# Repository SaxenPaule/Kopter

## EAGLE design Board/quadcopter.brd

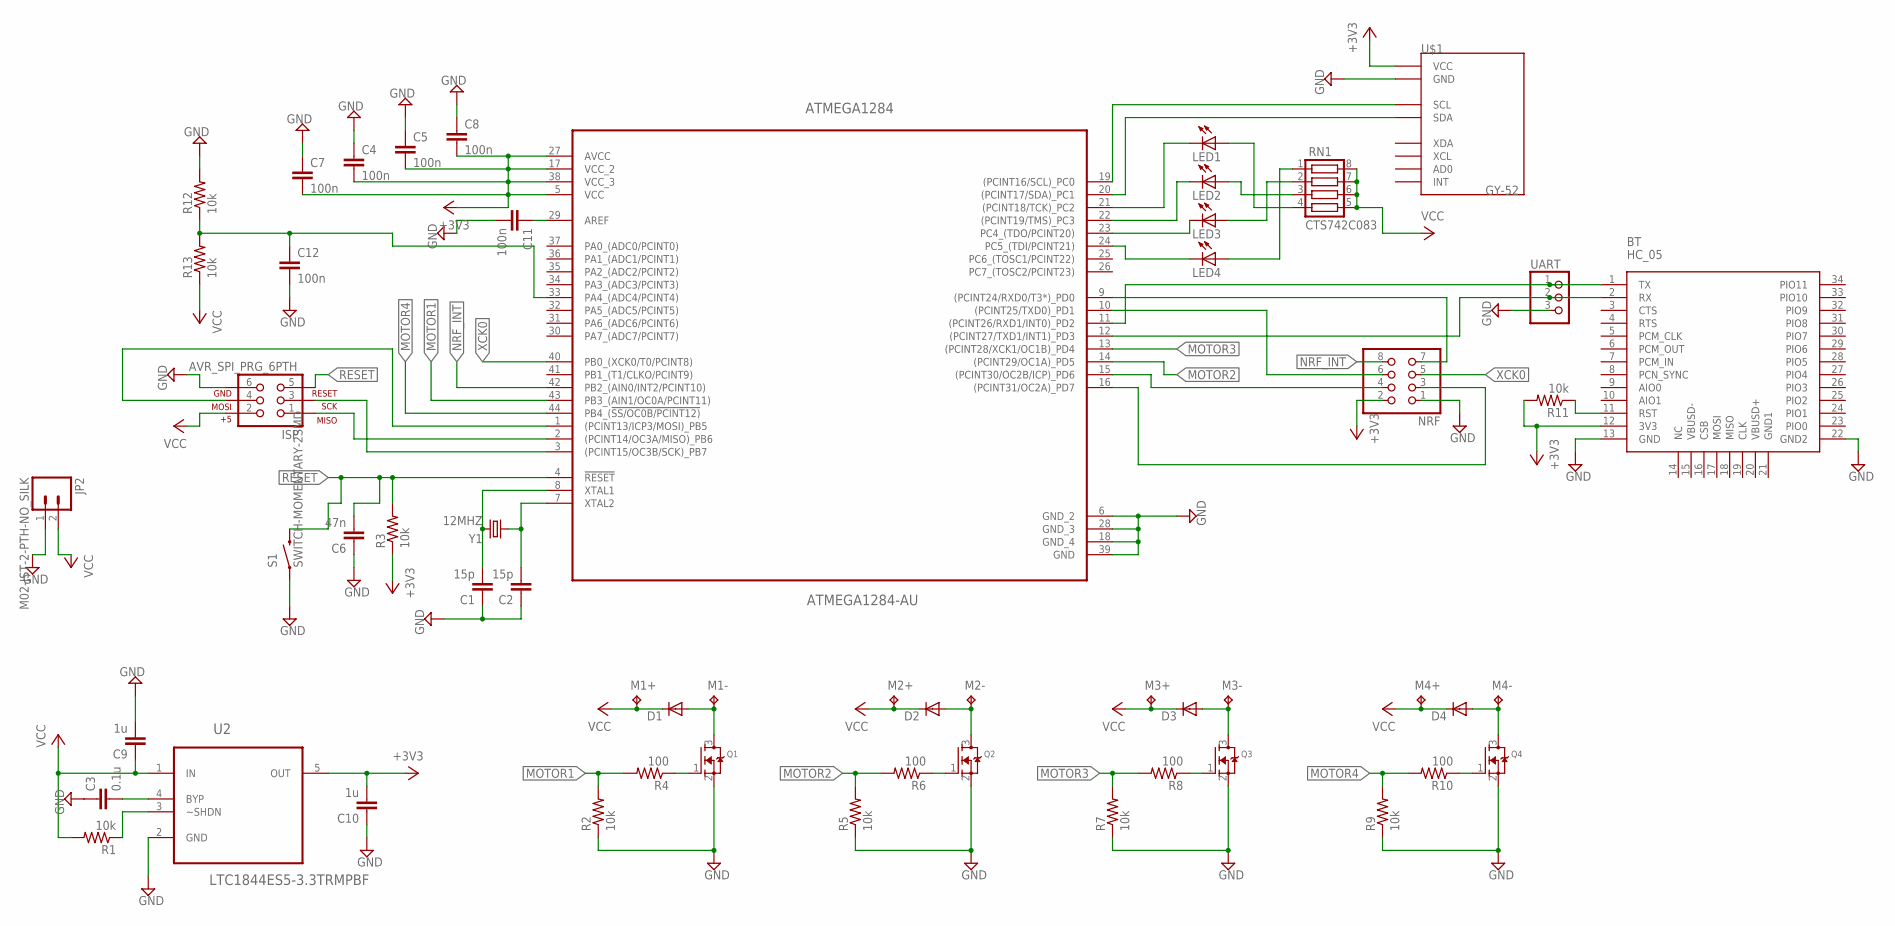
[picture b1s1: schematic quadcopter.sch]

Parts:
ATMEGA1284: ATMEGA1284-AU; QFP80P1200X1200X120-44N
BT: HC_05; BLUETOOTH_SMD
C1, C2: 15p; 0603-CAP
C3: 0.1u; 0603-CAP
C4, C5, C7, C8, C11, C12: 100n; 0603-CAP
C6: 47n; 0603-CAP
C9, C10: 1u; 0603-CAP
D1, D2, D3, D4: DIODE-SMB; SMB
ISP: AVR_SPI_PRG_6PTH; 2X3
JP2: M02-JST-2-PTH-NO_SILK; JST-2-PTH-NS
LED1, LED2, LED3, LED4: LEDCHIP-LED0805; CHIP-LED0805
M1+, M1-, M2+, M2-, M3+, M3-, M4+, M4-: TPTP20SQ; TP20SQ
NRF: PINHD-2X4; 2X04
Q1, Q2, Q3, Q4: MOSFET-NREFLOW; SOT23
R1, R2, R3, R5, R7, R9, R11, R12, R13: 10k; 0603-RES
R4, R6, R8, R10: 100; 0603-RES
RN1: CTS742C083
S1: SWITCH-MOMENTARY-2SMD; TACTILE_SWITCH_SMD
U2: LTC1844ES5-3.3TRMPBF; SOT95P280X100-5N
U$1: GY-52; PDIP-8
UART: PINHD-1X3; 1X03
Y1: 12MHZ; TXC-SMD-CRYSTAL

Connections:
+3V3: ATMEGA1284.5 (VCC), ATMEGA1284.17 (VCC_2), ATMEGA1284.27 (AVCC), ATMEGA1284.38 (VCC_3), BT.12 (3V3), C4.2, C5.2, C7.2, C8.2, C10.2, NRF.2, R3.1, R11.2, U2.5 (OUT), U$1.P$2 (VCC)
GND: ATMEGA1284.6 (GND_2), ATMEGA1284.18 (GND_4), ATMEGA1284.28 (GND_3), ATMEGA1284.39 (GND), BT.13 (GND), BT.22 (GND2), C1.1, C2.1, C3.1, C4.1, C5.1, C6.1, C7.1, C8.1, C9.2, C10.1, C11.2, C12.2, ISP.6, JP2.1, NRF.1, Q1.2 (S), Q2.2 (S), Q3.2 (S), Q4.2 (S), R2.1, R5.1, R7.1, R9.1, R12.2, S1.1, U2.2 (GND), U$1.P$8 (GND), UART.3
MOTOR1: ATMEGA1284.43 (PB3_(AIN1/OC0A/PCINT11)), R2.2, R4.2
MOTOR2: ATMEGA1284.14 ((PCINT29/OC1A)_PD5), R5.2, R6.2
MOTOR3: ATMEGA1284.13 ((PCINT28/XCK1/OC1B)_PD4), R7.2, R8.2
MOTOR4: ATMEGA1284.44 (PB4_(!SS/OC0B/PCINT12)), R9.2, R10.2
unnamed: ATMEGA1284.8 (XTAL1), C1.2, Y1.P$2 (2)
unnamed: ATMEGA1284.7 (XTAL2), C2.2, Y1.P$1 (1)
unnamed: ATMEGA1284.19 ((PCINT16/SCL)_PC0), U$1.P$6 (SCL)
unnamed: ATMEGA1284.1 ((PCINT13/ICP3/MOSI)_PB5), ISP.4
unnamed: ATMEGA1284.2 ((PCINT14/OC3A/MISO)_PB6), ISP.1
unnamed: ATMEGA1284.3 ((PCINT15/OC3B/SCK)_PB7), ISP.3
unnamed: ATMEGA1284.20 ((PCINT17/SDA)_PC1), U$1.P$7 (SDA)
unnamed: ATMEGA1284.10 ((PCINT25/TXD0)_PD1), NRF.6
unnamed: R1.1, U2.3 (~SHDN)
unnamed: C3.2, U2.4 (BYP)
unnamed: Q2.1 (G), R6.1
unnamed: Q1.1 (G), R4.1
unnamed: D2.A, M2-.TP, Q2.3 (D)
unnamed: D1.A, M1-.TP, Q1.3 (D)
unnamed: ATMEGA1284.11 ((PCINT26/RXD1/INT0)_PD2), BT.1 (TX), UART.1
unnamed: Q3.1 (G), R8.1
unnamed: D3.A, M3-.TP, Q3.3 (D)
unnamed: ATMEGA1284.9 ((PCINT24/RXD0/T3*)_PD0), NRF.7
unnamed: Q4.1 (G), R10.1
unnamed: D4.A, M4-.TP, Q4.3 (D)
unnamed: ATMEGA1284.15 ((PCINT30/OC2B/ICP)_PD6), NRF.4
unnamed: ATMEGA1284.16 ((PCINT31/OC2A)_PD7), NRF.3
unnamed: ATMEGA1284.12 ((PCINT27/TXD1/INT1)_PD3), BT.2 (RX), UART.2
unnamed: ATMEGA1284.24 (PC5_(TDI/PCINT21)), LED4.C
unnamed: BT.11 (RST), R11.1
unnamed: ATMEGA1284.23 (PC4_(TDO/PCINT20)), LED3.C
unnamed: ATMEGA1284.22 ((PCINT19/TMS)_PC3), LED2.C
unnamed: ATMEGA1284.21 ((PCINT18/TCK)_PC2), LED1.C
unnamed: LED4.A, RN1.1
unnamed: LED3.A, RN1.2
unnamed: LED2.A, RN1.3
unnamed: LED1.A, RN1.4
unnamed: ATMEGA1284.29 (AREF), C11.1
unnamed: ATMEGA1284.33 (PA4_(ADC4/PCINT4)), C12.1, R12.1, R13.2
NRF_INT: ATMEGA1284.42 (PB2_(AIN0/INT2/PCINT10)), NRF.8
RESET: ATMEGA1284.4 (!RESET), C6.2, ISP.5, R3.2, S1.3 (2)
VCC: C9.1, D1.C, D2.C, D3.C, D4.C, ISP.2, JP2.2, M1+.TP, M2+.TP, M3+.TP, M4+.TP, R1.2, R13.1, RN1.5, RN1.6, RN1.7, RN1.8, U2.1 (IN)
XCK0: ATMEGA1284.40 (PB0_(XCK0/T0/PCINT8)), NRF.5

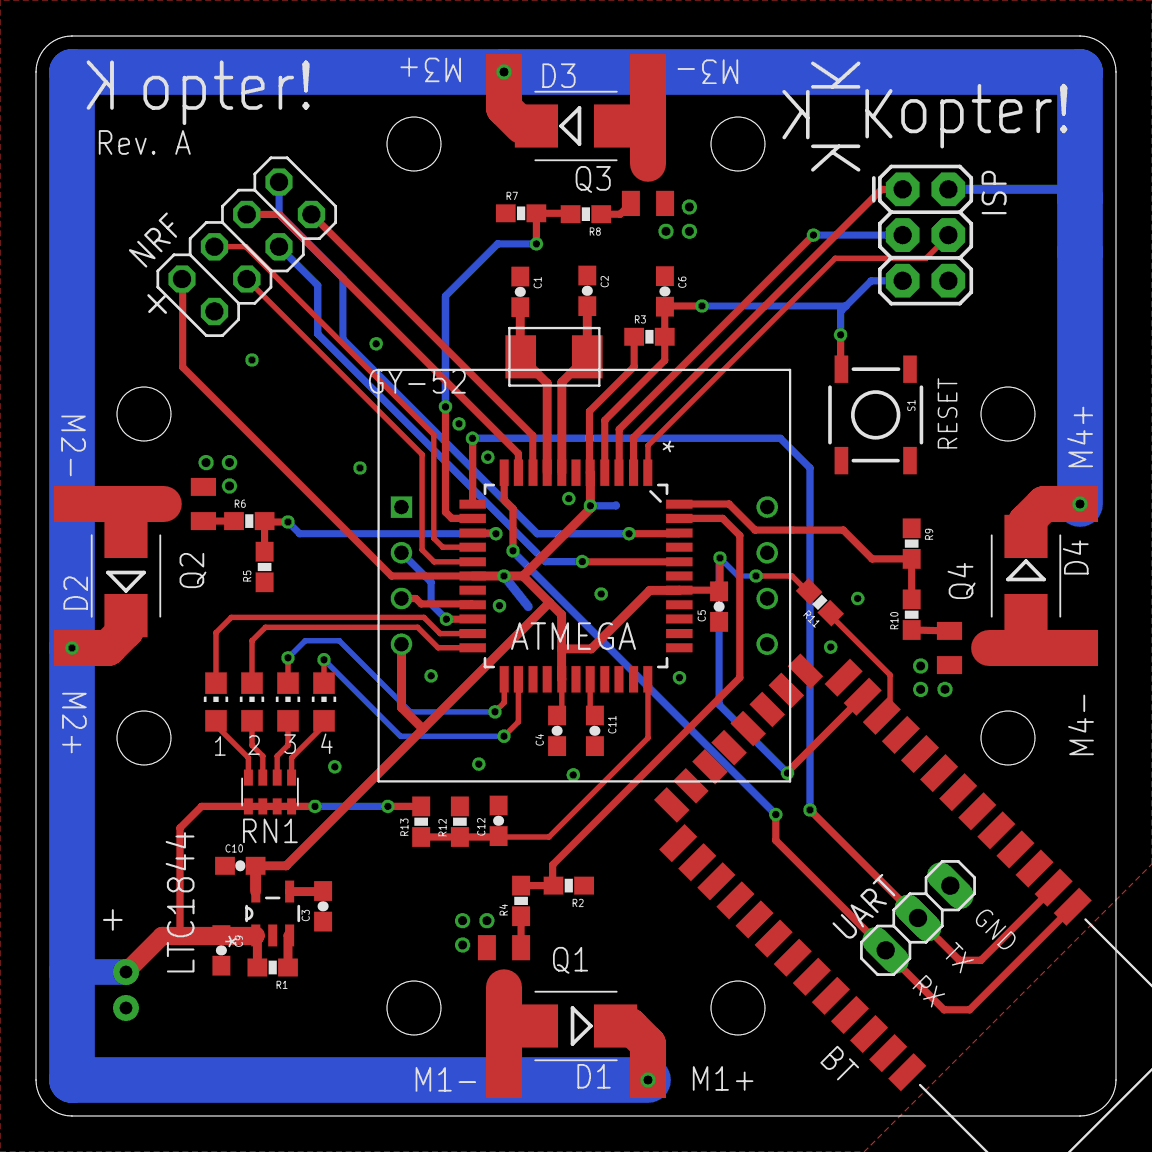
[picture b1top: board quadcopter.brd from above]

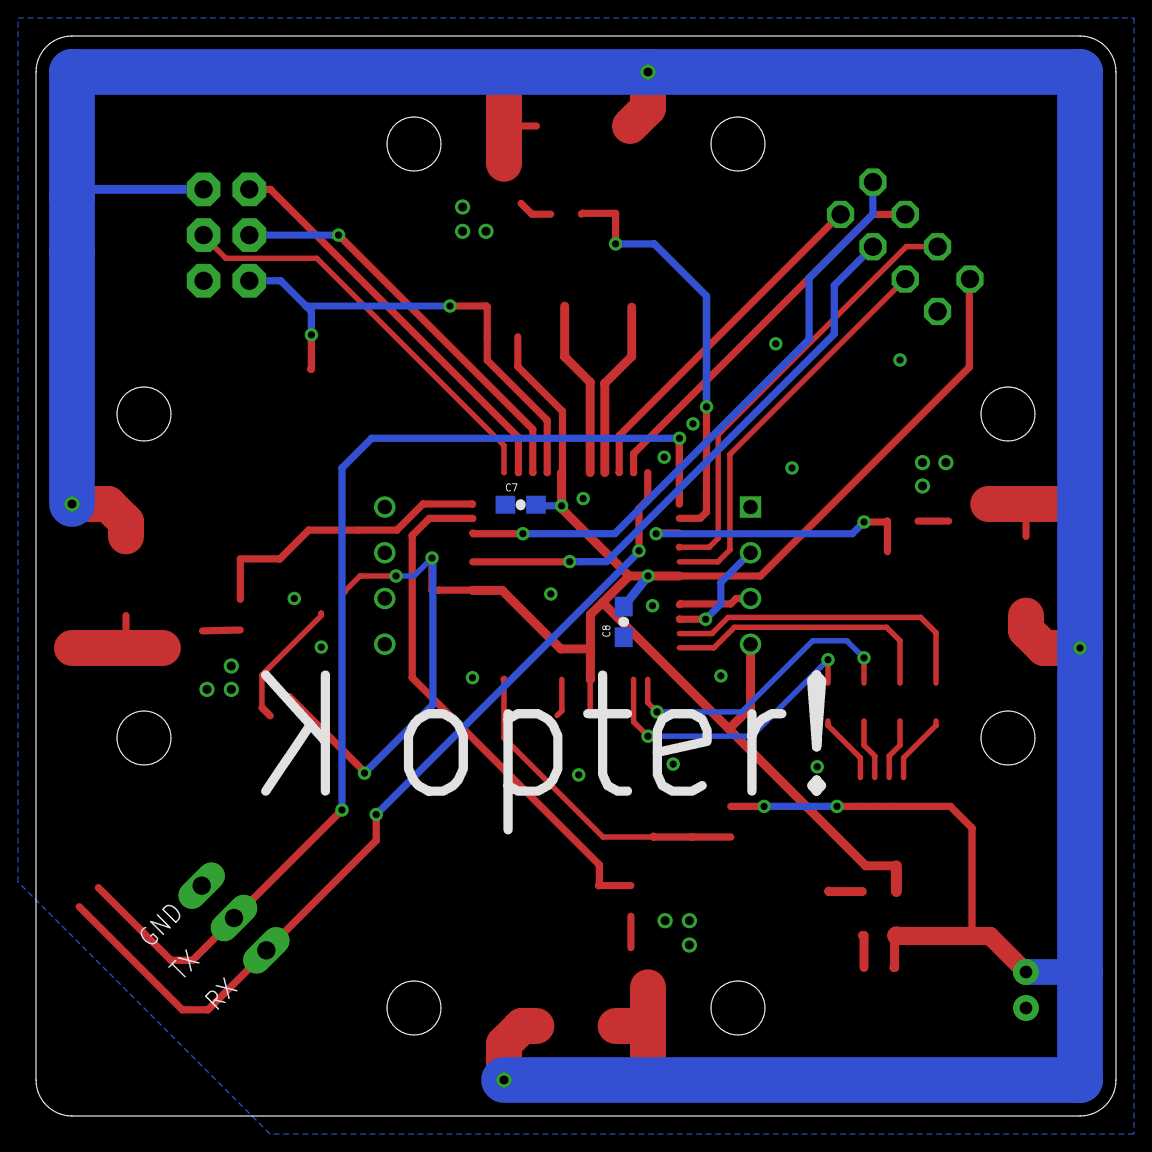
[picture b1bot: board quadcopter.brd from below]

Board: 2 copper layers, 60.0 x 60.0 mm, 56 parts (2 on the bottom side), 44 nets.

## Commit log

2014-05-29 added board layout
2014-05-29 Bestellte Boardversion
2014-06-02 Fix in Powersupply
    0.1uF instead of 1uF for bypass capacitor

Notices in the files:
parts and their libraries:
SparkFun-Connectors: Licensing: CC v3.0 Share-Alike You are welcome to use this library for commercial purposes.
